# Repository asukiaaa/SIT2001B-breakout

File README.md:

# SIT2001B-breakout

A breakout board of mems SIT2001B with a regulator.

[Schematic](./docs/SIT2001B-breakout.pdf).

## Components

- [SIT2001B 16MHz](https://akizukidenshi.com/catalog/g/gI-11094/)
- [NJM2866F33 3.3V 100mA](https://akizukidenshi.com/catalog/g/gI-05448/)
- 10k 0603
- 0.1uf (more than 14V) 0603
- 15pf 0603

## License

MIT

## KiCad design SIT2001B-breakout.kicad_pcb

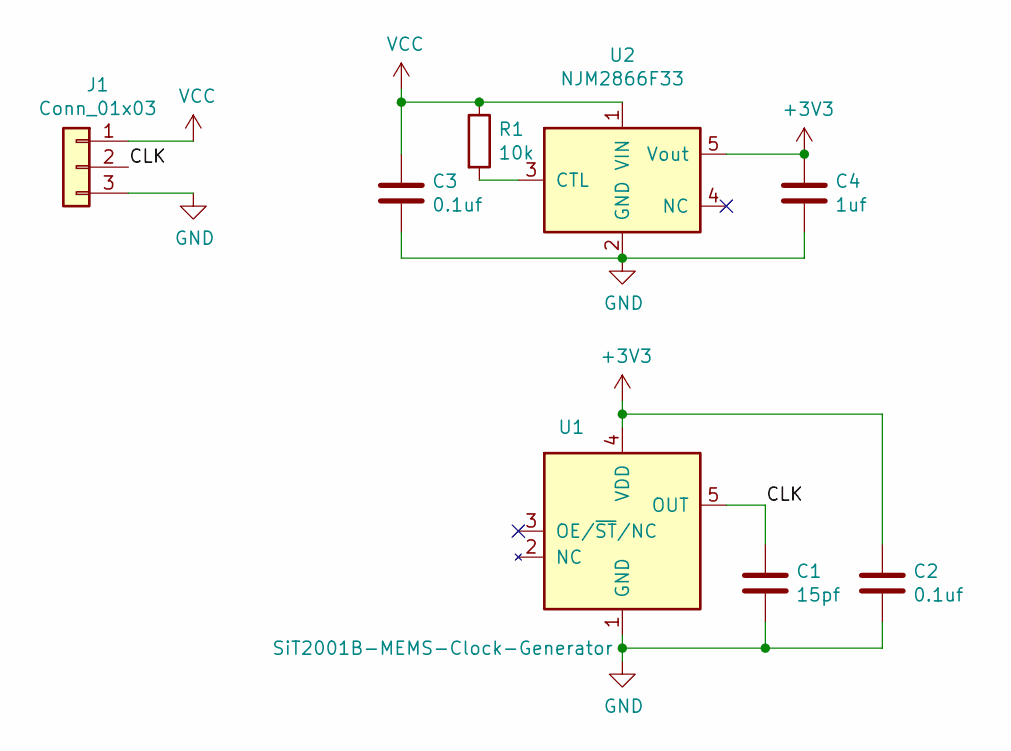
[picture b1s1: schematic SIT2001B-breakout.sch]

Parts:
C1: 15pf; C_0603_1608Metric
C2, C3: 0.1uf; C_0603_1608Metric
C4: 1uf; C_0603_1608Metric
J1: Conn_01x03; Pin_1x03_P2.54mm_nosilk
R1: 10k; R_0603_1608Metric
U1: SiT2001B-MEMS-Clock-Generator; SOT-23-5
U2: NJM2866F33; SOT-23-5

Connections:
+3V3: C2.1, C4.1, U1.4 (VDD), U2.5 (Vout)
/CLK: C1.1, J1.2, U1.5 (OUT)
GND: C1.2, C2.2, C3.2, C4.2, J1.3, U1.1 (GND), U2.2 (GND)
unnamed: R1.2, U2.3 (CTL)
VCC: C3.1, J1.1, R1.1, U2.1 (VIN)

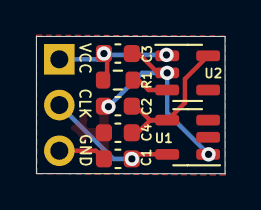
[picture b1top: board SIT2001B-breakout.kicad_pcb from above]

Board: 2 copper layers, 10.5 x 7.6 mm, 8 parts (0 on the bottom side), 5 nets.

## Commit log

2021-06-08 Correct warning and error of drc
2021-06-08 Remove kicad_pcb-bak and sch-bak from git
2021-06-28 Plot schematic as pdf
